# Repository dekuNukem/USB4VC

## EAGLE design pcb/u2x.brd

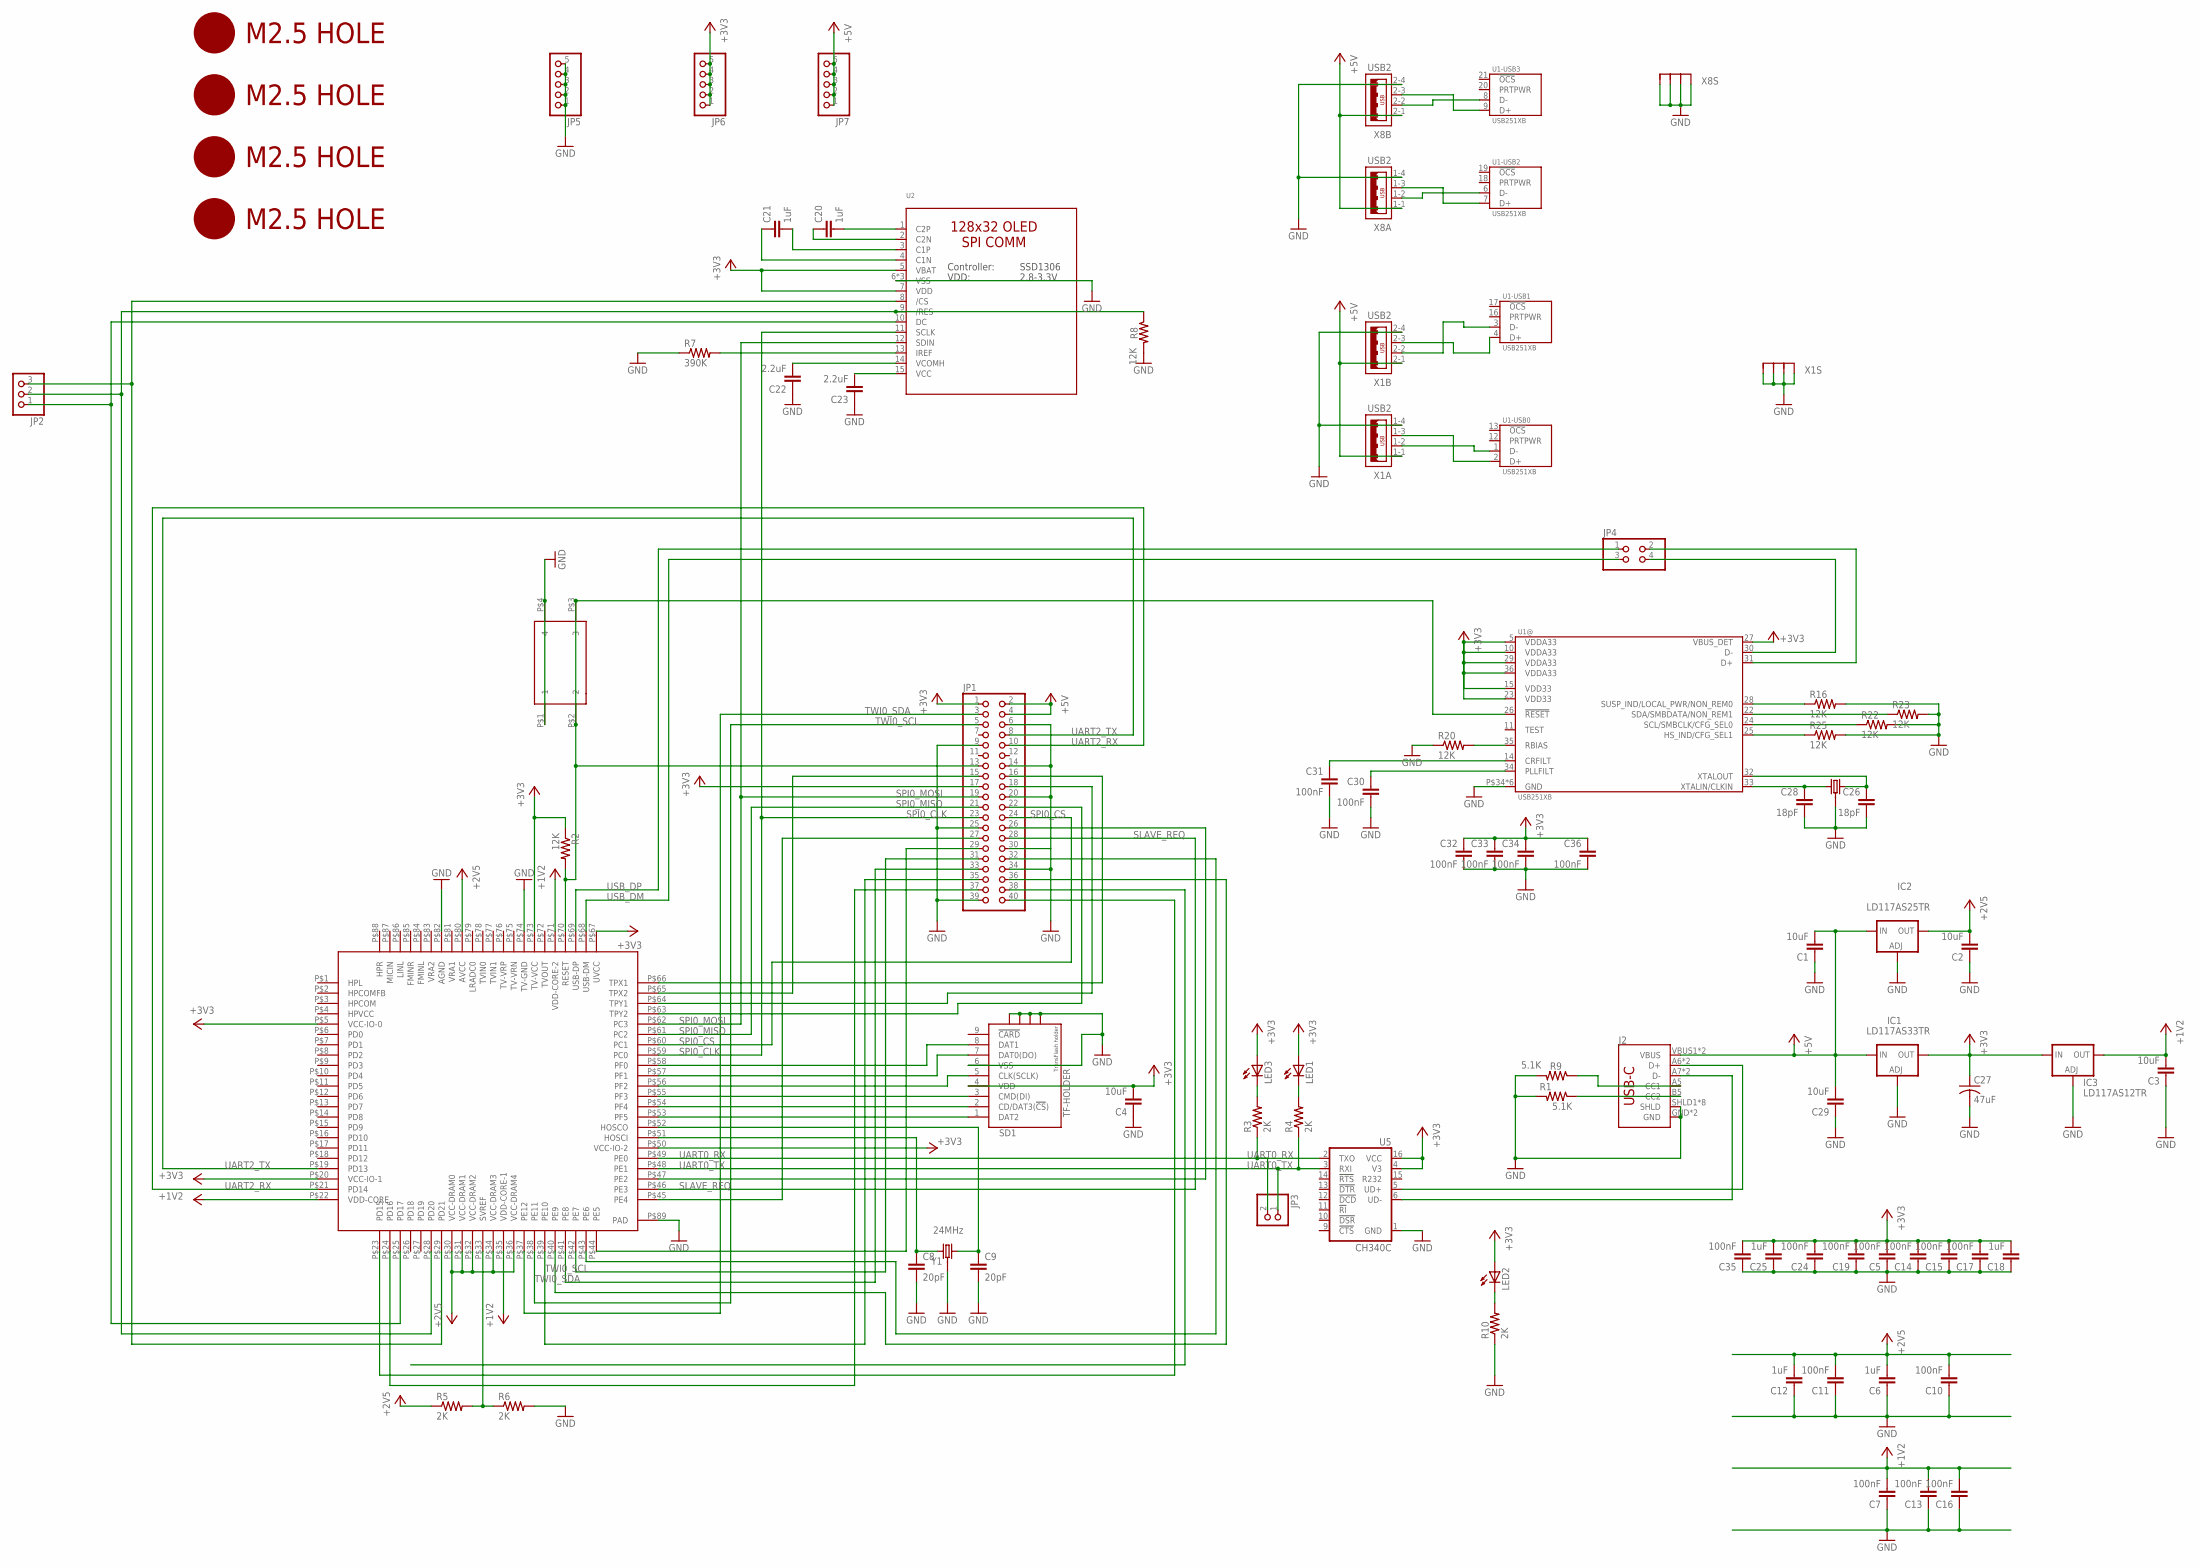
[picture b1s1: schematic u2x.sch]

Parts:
C1, C2, C3, C4, C29: 10uF; 0805
C5, C7, C10, C11, C13, C14, C15, C16, C17, C19, C24, C30, C31, C32, C33, C34, C35, C36: 100nF; 0805
C6, C12, C18, C20, C21, C25: 1uF; 0805
C8, C9: 20pF; 0805
C22, C23: 2.2uF; 0805
C26, C28: 18pF; 0805
C27: 47uF; C1210
IC1: LD117AS33TR; SOT223
IC2: LD117AS25TR; SOT223
IC3: LD117AS12TR; SOT223
J2: USB_C16PIN; USB-C-16P
JP1: PINHD-2X20-BIG; 2X20-BIG
JP2: PINHD-1X3CB; 1X03-CLEANBIG
JP3: PINHD-1X2; 1X02
JP4: PINHD-2X2; 2X02
JP5, JP6, JP7: PINHD-1X5; 1X05
LED1, LED2, LED3: LEDCHIP-LED0805; CHIP-LED0805
R1, R9: 5.1K; 0805
R2, R8, R16, R20, R22, R23, R25: 12K; 0805
R3, R4, R5, R6, R10: 2K; 0805
R7: 390K; 0805
SD1: TF-HOLDER; TF-PULL
SW20: 324_SW; 342_SWICH_FOOT
U1: USB251XB; QFN-36
U2: LUL_DISP_OLED_UG-2864HSWEG01; LUL_UG-2864HSWEG01_1.3_WRAPAROUND
U5: CH340C; SO016
U$1: F1C100S_DEV; MQFN88
U$2, U$3, U$4, U$5: M2.5HOLE
U$16: CRYSTAL-GROUNDED; CRYSTAL-SMD-5X3
X1, X8: USB2
Y1: 24MHz; CRYSTAL-SMD-3.2X2.5MM

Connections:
+1V2: C3.2, C7.2, C13.2, C16.2, IC3.4 (OUT), U$1.P$22 (VDD-CORE), U$1.P$35 (VDD-CORE-1), U$1.P$71 (VDD-CORE-2)
+2V5: C2.2, C6.2, C10.2, C11.2, C12.2, IC2.4 (OUT), R5.1, U$1.P$30 (VCC-DRAM0), U$1.P$31 (VCC-DRAM1), U$1.P$32 (VCC-DRAM2), U$1.P$34 (VCC-DRAM3), U$1.P$36 (VCC-DRAM4), U$1.P$80 (AVCC)
+3V3: C4.2, C5.2, C14.2, C15.2, C17.2, C18.2, C19.2, C24.2, C25.2, C27.1, C32.1, C33.1, C34.1, C35.2, C36.1, IC1.4 (OUT), IC3.3 (IN), JP1.1, JP1.17, JP6.1, JP6.2, JP6.3, JP6.4, JP6.5, LED1.A, LED2.A, LED3.A, R2.1, SD1.4 (VDD), U1.5 (VDDA33), U1.10 (VDDA33), U1.15 (VDD33), U1.23 (VDD33), U1.27 (VBUS_DET), U1.29 (VDDA33), U1.36 (VDDA33), U2.5 (VBAT), U2.7 (VDD), U5.4 (V3), U5.16 (VCC), U$1.P$5 (VCC-IO-0), U$1.P$20 (VCC-IO-1), U$1.P$50 (VCC-IO-2), U$1.P$67 (UVCC), U$1.P$73 (TV-VCC)
+5V: C1.2, C29.2, IC1.3 (IN), IC2.3 (IN), J2.VBUS1 (VBUS), J2.VBUS2 (VBUS), JP1.2, JP1.4, JP7.1, JP7.2, JP7.3, JP7.4, JP7.5, X1.1-1 (1), X1.2-1 (1), X8.1-1 (1), X8.2-1 (1)
GND: C1.1, C2.1, C3.1, C4.1, C5.1, C6.1, C7.1, C8.2, C9.2, C10.1, C11.1, C12.1, C13.1, C14.1, C15.1, C16.1, C17.1, C18.1, C19.1, C22.1, C23.1, C24.1, C25.1, C26.2, C27.2, C28.2, C29.1, C30.2, C31.2, C32.2, C33.2, C34.2, C35.1, C36.2, IC1.1 (ADJ), IC2.1 (ADJ), IC3.1 (ADJ), J2.GND, J2.GND2 (GND), J2.SHLD1 (SHLD), J2.SHLD2 (SHLD), J2.SHLD3 (SHLD), J2.SHLD4 (SHLD), J2.SHLD5 (SHLD), J2.SHLD6 (SHLD), J2.SHLD7 (SHLD), J2.SHLD8 (SHLD), JP1.6, JP1.9, JP1.14, JP1.20, JP1.25, JP1.30, JP1.34, JP1.39, JP5.1, JP5.2, JP5.3, JP5.4, JP5.5, R1.2, R6.2, R7.1, R8.2, R9.2, R10.1, R16.2, R20.1, R22.2, R23.2, R25.2, SD1.6 (VSS), SD1.S1, SD1.S2, SD1.S3, SD1.S4, SW20.P$1 (1), SW20.P$4 (4), U1.P$34 (GND), U1.P$35 (GND), U1.P$36 (GND), U1.P$37 (GND), U1.P$38 (GND), U1.PAD (GND), U2.6 (VSS), U2.16 (VSS), U2.17 (VSS), U5.1 (GND), U$1.P$74 (TV-GND), U$1.P$82 (AGND), U$1.P$89 (PAD), U$16.2 (3), U$16.4 (3), X1.1-4 (4), X1.2-4 (4), X1.M1 (S1), X1.M2 (S2), X1.M3 (S3), X1.M4 (S4), X8.1-4 (4), X8.2-4 (4), X8.M1 (S1), X8.M2 (S2), X8.M3 (S3), X8.M4 (S4), Y1.2 (3), Y1.4 (3)
unnamed: SD1.8 (DAT1), U$1.P$58 (PF0)
unnamed: J2.A5 (CC1), R9.1
unnamed: C8.1, U$1.P$51 (HOSCI), Y1.1
unnamed: C9.1, U$1.P$52 (HOSCO), Y1.3 (2)
unnamed: LED1.C, R4.2
unnamed: LED3.C, R3.2
unnamed: J2.B5 (CC2), R1.1
unnamed: SD1.7 (DAT0(DO)), U$1.P$57 (PF1)
unnamed: SD1.5 (CLK(SCLK)), U$1.P$56 (PF2)
unnamed: SD1.3 (CMD(DI)), U$1.P$55 (PF3)
unnamed: SD1.2 (CD/DAT3(!CS!)), U$1.P$54 (PF4)
unnamed: SD1.1 (DAT2), U$1.P$53 (PF5)
unnamed: U1.2 (D+), X1.1-3 (3)
unnamed: R5.2, R6.1, U$1.P$33 (SVREF)
unnamed: U1.1 (D-), X1.1-2 (2)
unnamed: J2.A6 (D+), J2.B6 (D+), U5.5 (UD+)
unnamed: JP1.13, R2.2, SW20.P$2 (2), SW20.P$3 (3), U1.26 (!RESET), U$1.P$70 (RESET)
unnamed: J2.A7 (D-), J2.B7 (D-), U5.6 (UD-)
unnamed: JP1.26, U$1.P$47 (PE2)
unnamed: JP1.27, U$1.P$45 (PE4)
unnamed: JP1.18, U$1.P$64 (TPY1)
unnamed: JP1.22, U$1.P$63 (TPY2)
unnamed: JP1.15, U$1.P$65 (TPX2)
unnamed: JP1.16, U$1.P$66 (TPX1)
unnamed: JP1.29, U$1.P$44 (PE5)
unnamed: JP1.32, U$1.P$43 (PE6)
unnamed: JP1.31, U$1.P$42 (PE7)
unnamed: JP1.33, U$1.P$41 (PE8)
unnamed: JP1.36, U$1.P$40 (PE9)
unnamed: JP1.35, U$1.P$39 (PE10)
unnamed: JP1.40, U$1.P$23 (PD15)
unnamed: JP1.37, U$1.P$24 (PD16)
unnamed: C20.2, U2.1 (C2P)
unnamed: C20.1, U2.2 (C2N)
unnamed: C21.2, U2.3 (C1P)
unnamed: C21.1, U2.4 (C1N)
unnamed: R7.2, U2.13 (IREF)
unnamed: C22.2, U2.14 (VCOMH)
unnamed: C23.2, U2.15 (VCC)
unnamed: JP2.3, U2.8 (/CS), U$1.P$29 (PD21)
unnamed: JP2.2, R8.1, U2.9 (/RES), U$1.P$28 (PD20)
unnamed: JP2.1, U2.10 (DC), U$1.P$25 (PD17)
unnamed: U1.4 (D+), X1.2-3 (3)
unnamed: U1.3 (D-), X1.2-2 (2)
unnamed: U1.6 (D-), X8.1-2 (2)
unnamed: U1.7 (D+), X8.1-3 (3)
unnamed: U1.8 (D-), X8.2-2 (2)
unnamed: U1.9 (D+), X8.2-3 (3)
unnamed: JP4.4, U1.30 (D-)
unnamed: JP4.2, U1.31 (D+)
unnamed: LED2.C, R10.2
unnamed: R20.2, U1.35 (RBIAS)
unnamed: C28.1, U1.33 (XTALIN/CLKIN), U$16.1 (2)
unnamed: C26.1, U1.32 (XTALOUT), U$16.3 (1)
unnamed: C31.1, U1.14 (CRFILT)
unnamed: C30.1, U1.34 (PLLFILT)
unnamed: R16.1, U1.28 (SUSP_IND/LOCAL_PWR/NON_REM0)
unnamed: R25.1, U1.25 (HS_IND/CFG_SEL1)
unnamed: R23.1, U1.22 (SDA/SMBDATA/NON_REM1)
unnamed: R22.1, U1.24 (SCL/SMBCLK/CFG_SEL0)
SLAVE_REQ: JP1.28, U$1.P$46 (PE3)
SPI0_CLK: JP1.23, U2.11 (SCLK), U$1.P$59 (PC0)
SPI0_CS: JP1.24, U$1.P$60 (PC1)
SPI0_MISO: JP1.21, U$1.P$61 (PC2)
SPI0_MOSI: JP1.19, U2.12 (SDIN), U$1.P$62 (PC3)
TWI0_SCL: JP1.5, U$1.P$38 (PE11)
TWI0_SDA: JP1.3, U$1.P$37 (PE12)
UART0_RX: JP3.2, R3.1, U5.2 (TXO), U$1.P$49 (PE0)
UART0_TX: JP3.1, R4.1, U5.3 (RXI), U$1.P$48 (PE1)
UART2_RX: JP1.10, U$1.P$21 (PD14)
UART2_TX: JP1.8, U$1.P$19 (PD13)
USB_DM: JP4.3, U$1.P$68 (USB-DM)
USB_DP: JP4.1, U$1.P$69 (USB-DP)

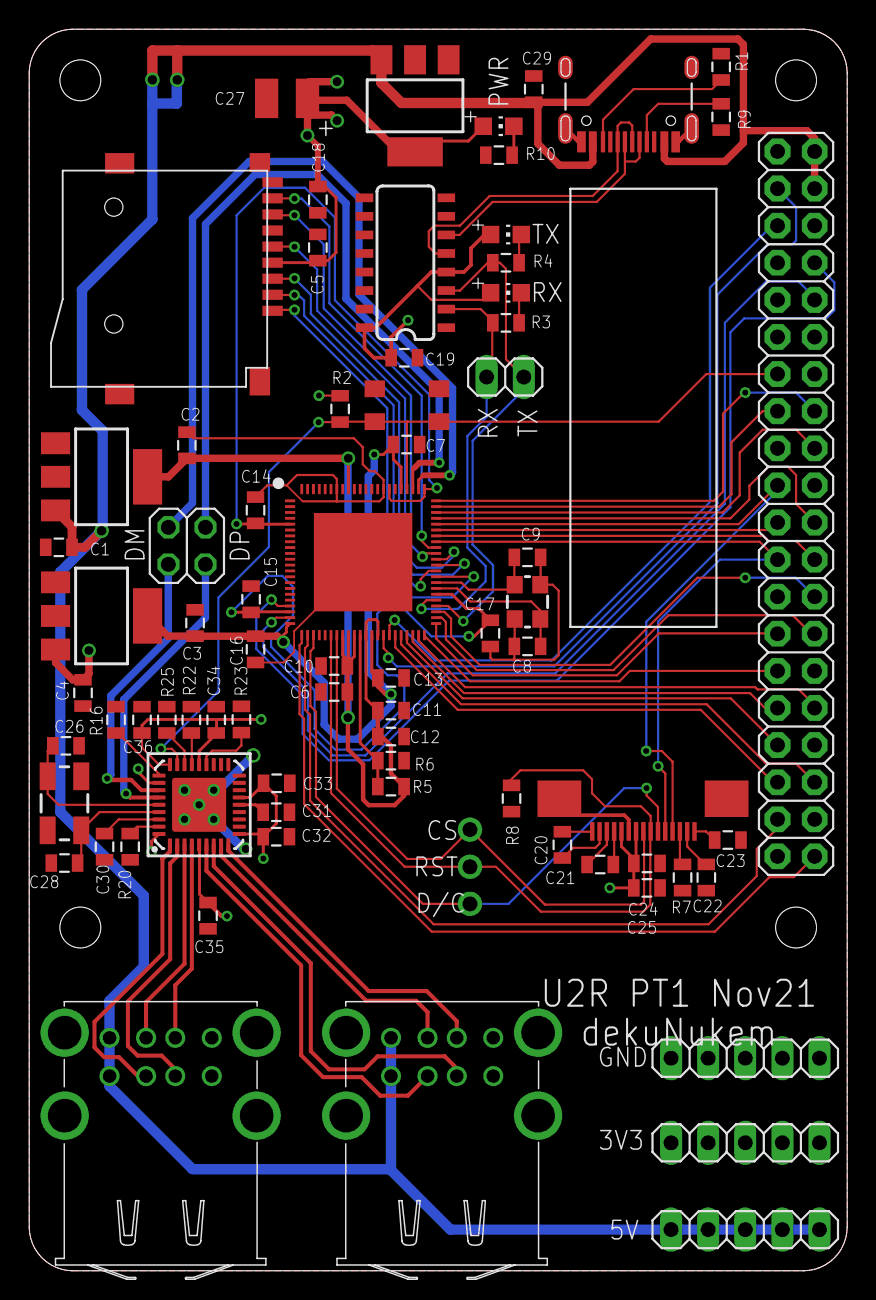
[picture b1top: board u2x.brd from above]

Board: 2 copper layers, 56.0 x 85.0 mm, 79 parts (0 on the bottom side), 78 nets.

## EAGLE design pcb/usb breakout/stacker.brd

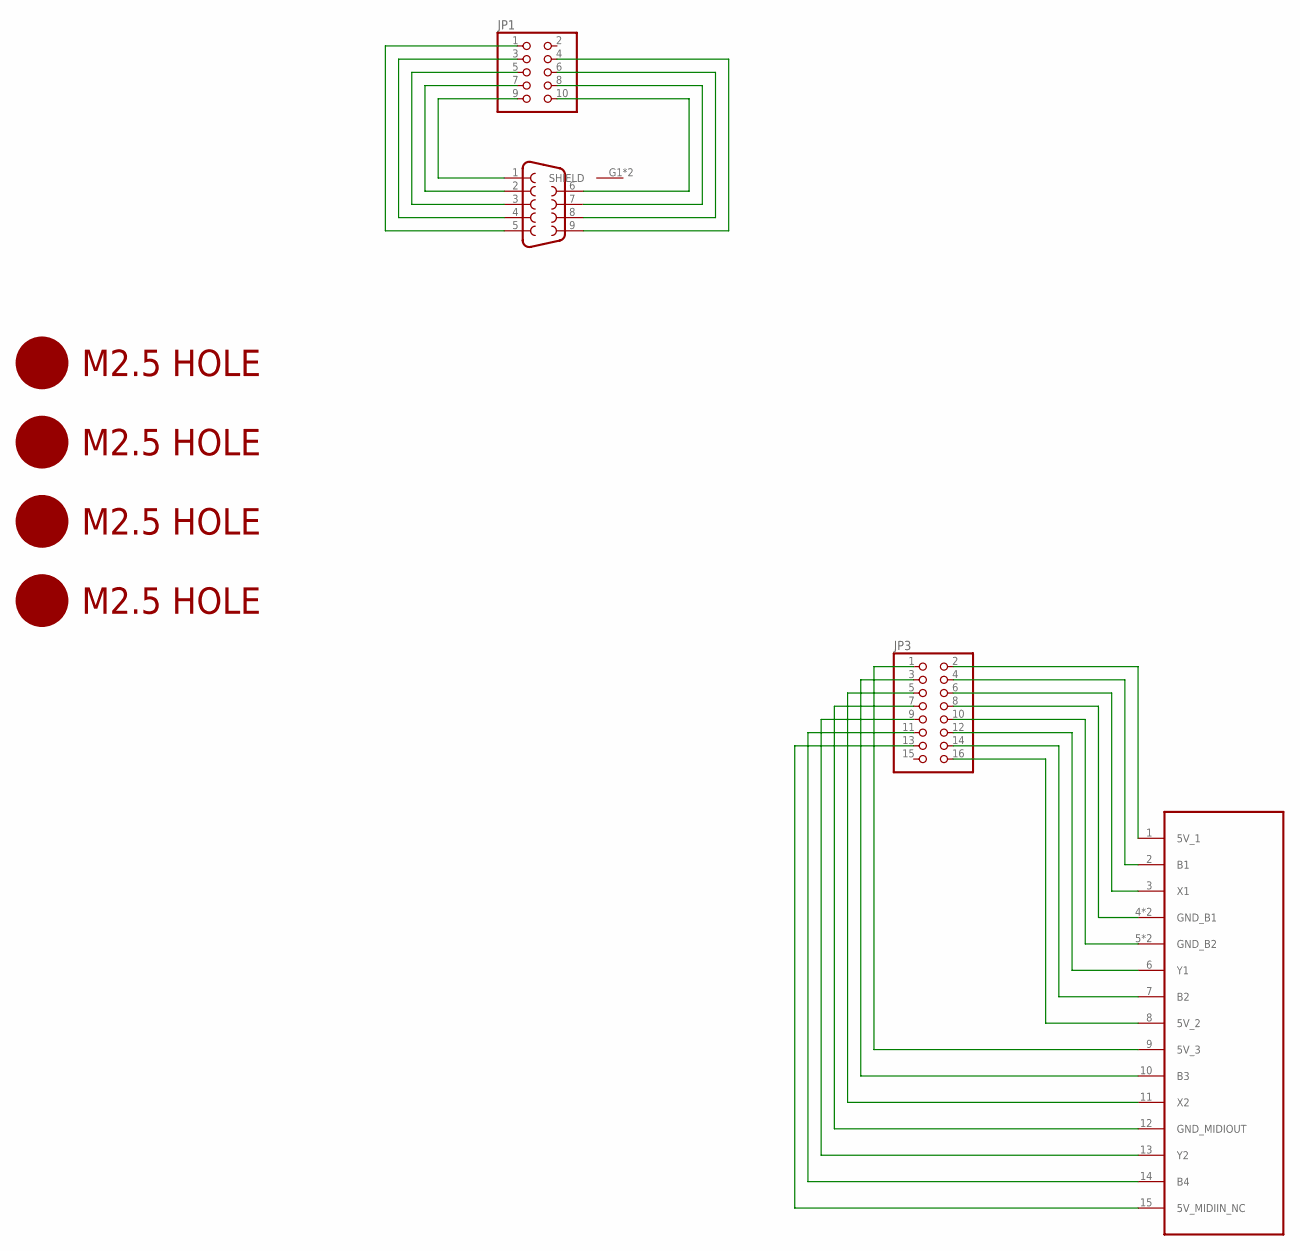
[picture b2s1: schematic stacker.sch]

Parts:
J5: DB9MALE; DB9_MALE
JP1: PINHD-2X5; 2X05
JP3: PINHD-2X8; 2X08
U$2, U$3, U$4, U$5: M2.5HOLE
U$11: GAMEPORT_15P; DA15

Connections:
unnamed: J5.1, JP1.9
unnamed: J5.2, JP1.7
unnamed: J5.3, JP1.5
unnamed: J5.4, JP1.3
unnamed: J5.5, JP1.1
unnamed: J5.6, JP1.10
unnamed: J5.7, JP1.8
unnamed: J5.8, JP1.6
unnamed: J5.9, JP1.4
unnamed: JP3.2, U$11.1 (5V_1)
unnamed: JP3.4, U$11.2 (B1)
unnamed: JP3.6, U$11.3 (X1)
unnamed: JP3.8, U$11.4 (GND_B1), U$11.G1 (GND_B1)
unnamed: JP3.10, U$11.5 (GND_B2), U$11.G2 (GND_B2)
unnamed: JP3.12, U$11.6 (Y1)
unnamed: JP3.14, U$11.7 (B2)
unnamed: JP3.16, U$11.8 (5V_2)
unnamed: JP3.1, U$11.9 (5V_3)
unnamed: JP3.3, U$11.10 (B3)
unnamed: JP3.5, U$11.11 (X2)
unnamed: JP3.7, U$11.12 (GND_MIDIOUT)
unnamed: JP3.9, U$11.13 (Y2)
unnamed: JP3.11, U$11.14 (B4)
unnamed: JP3.13, U$11.15 (5V_MIDIIN_NC)

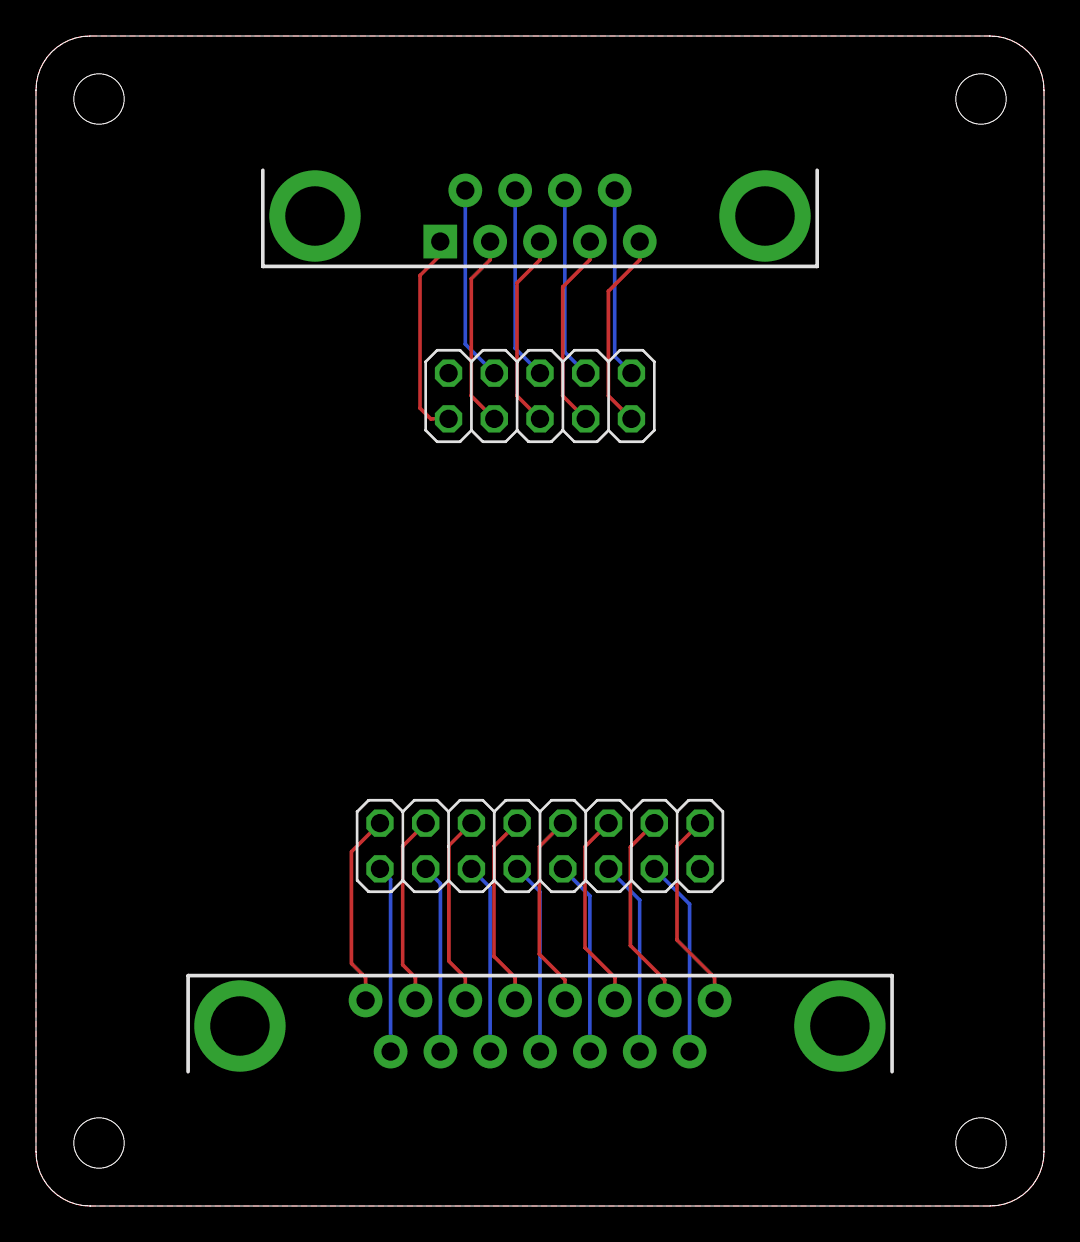
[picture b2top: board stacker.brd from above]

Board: 2 copper layers, 56.0 x 65.0 mm, 8 parts (0 on the bottom side), 24 nets.

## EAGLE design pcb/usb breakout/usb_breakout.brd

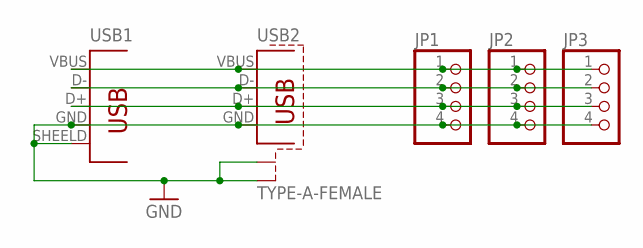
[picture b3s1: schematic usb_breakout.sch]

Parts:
JP1, JP2, JP3: PINHD-1X4; 1X04
USB1: TYPE-A-MALE-SHILED; TYPE-A-MALE
USB2: TYPE-A-FEMALE

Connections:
GND: JP1.4, JP2.4, JP3.4, USB1.GND (4), USB1.SHEELD (5), USB2.GND, USB2.S1, USB2.S2
unnamed: JP1.1, JP2.1, JP3.1, USB1.VBUS (1), USB2.VBUS (VCC)
unnamed: JP1.2, JP2.2, JP3.2, USB1.D- (2), USB2.D-
unnamed: JP1.3, JP2.3, JP3.3, USB1.D+ (3), USB2.D+

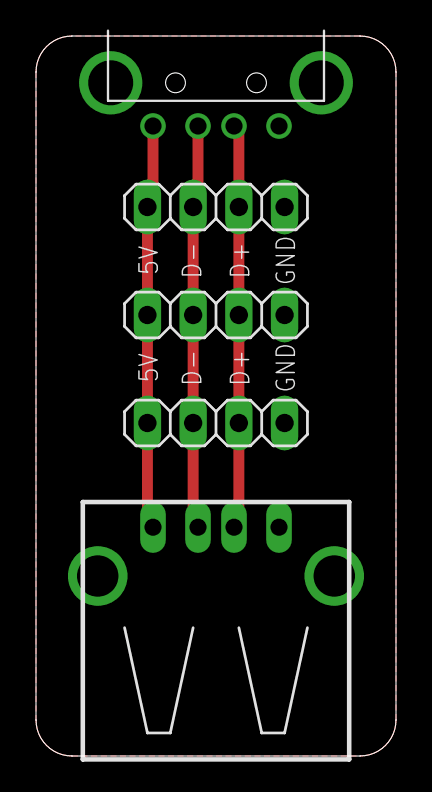
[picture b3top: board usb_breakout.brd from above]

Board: 2 copper layers, 20.0 x 40.0 mm, 5 parts (0 on the bottom side), 4 nets.

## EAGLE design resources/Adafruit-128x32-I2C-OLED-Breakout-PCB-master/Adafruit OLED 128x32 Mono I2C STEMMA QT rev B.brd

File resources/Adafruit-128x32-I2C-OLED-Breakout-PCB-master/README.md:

# PCB for the Adafruit 128x32 I2C OLED breakout board

<a href="http://www.adafruit.com/products/931"><br/>Click here to purchase one from the Adafruit shop</a>

__Format is EagleCAD schematic and board layout__

These displays are small, only about 1" diagonal, but very readable due to the high contrast of an OLED display. This display is made of 128x32 individual white OLED pixels, each one is turned on or off by the controller chip. Because the display makes its own light, no backlight is required. This reduces the power required to run the OLED and is why the display has such high contrast; we really like this miniature display for its crispness!

The driver chip SSD1306, __communicates via I2C only.__ 3 pins are required to communicate with the chip in the OLED display, two of which are I2C data/clock pins.

The OLED and driver require a 3.3V power supply and 3.3V logic levels for communication. To make it easier for our customers to use, we've added a 3.3v regulator and level shifter on board! This makes it compatible with any 5V microcontroller, such as the Arduino.

The power requirements depend a little on how much of the display is lit but on average the display uses about 20mA from the 3.3V supply. Built into the OLED driver is a simple switch-cap charge pump that turns 3.3v-5v into a high voltage drive for the OLEDs, making it one of the easiest ways to get an OLED into your project!

Of course, we wouldn't leave you with a datasheet and a "good luck": [We have a detailed tutorial](http://learn.adafruit.com/monochrome-oled-breakouts) and [example code in the form of an Arduino library](https://github.com/adafruit/Adafruit_SSD1306) for text and graphics. You'll need a microcontroller with more than 512 bytes of RAM since the display must be buffered.

You can download our SSD1306 OLED display Arduino library from github which comes with example code. The library can print text, bitmaps, pixels, rectangles, circles and lines. It uses 512 bytes of RAM since it needs to buffer the entire display but its very fast! The code is simple to adapt to any other microcontroller.

## License
Adafruit invests time and resources providing this open source design,
please support Adafruit and open-source hardware by purchasing
products from Adafruit!

Designed by Limor Fried/Ladyada for Adafruit Industries.
Creative Commons Attribution, Share-Alike license, check license.txt for more information
All text above must be included in any redistribution

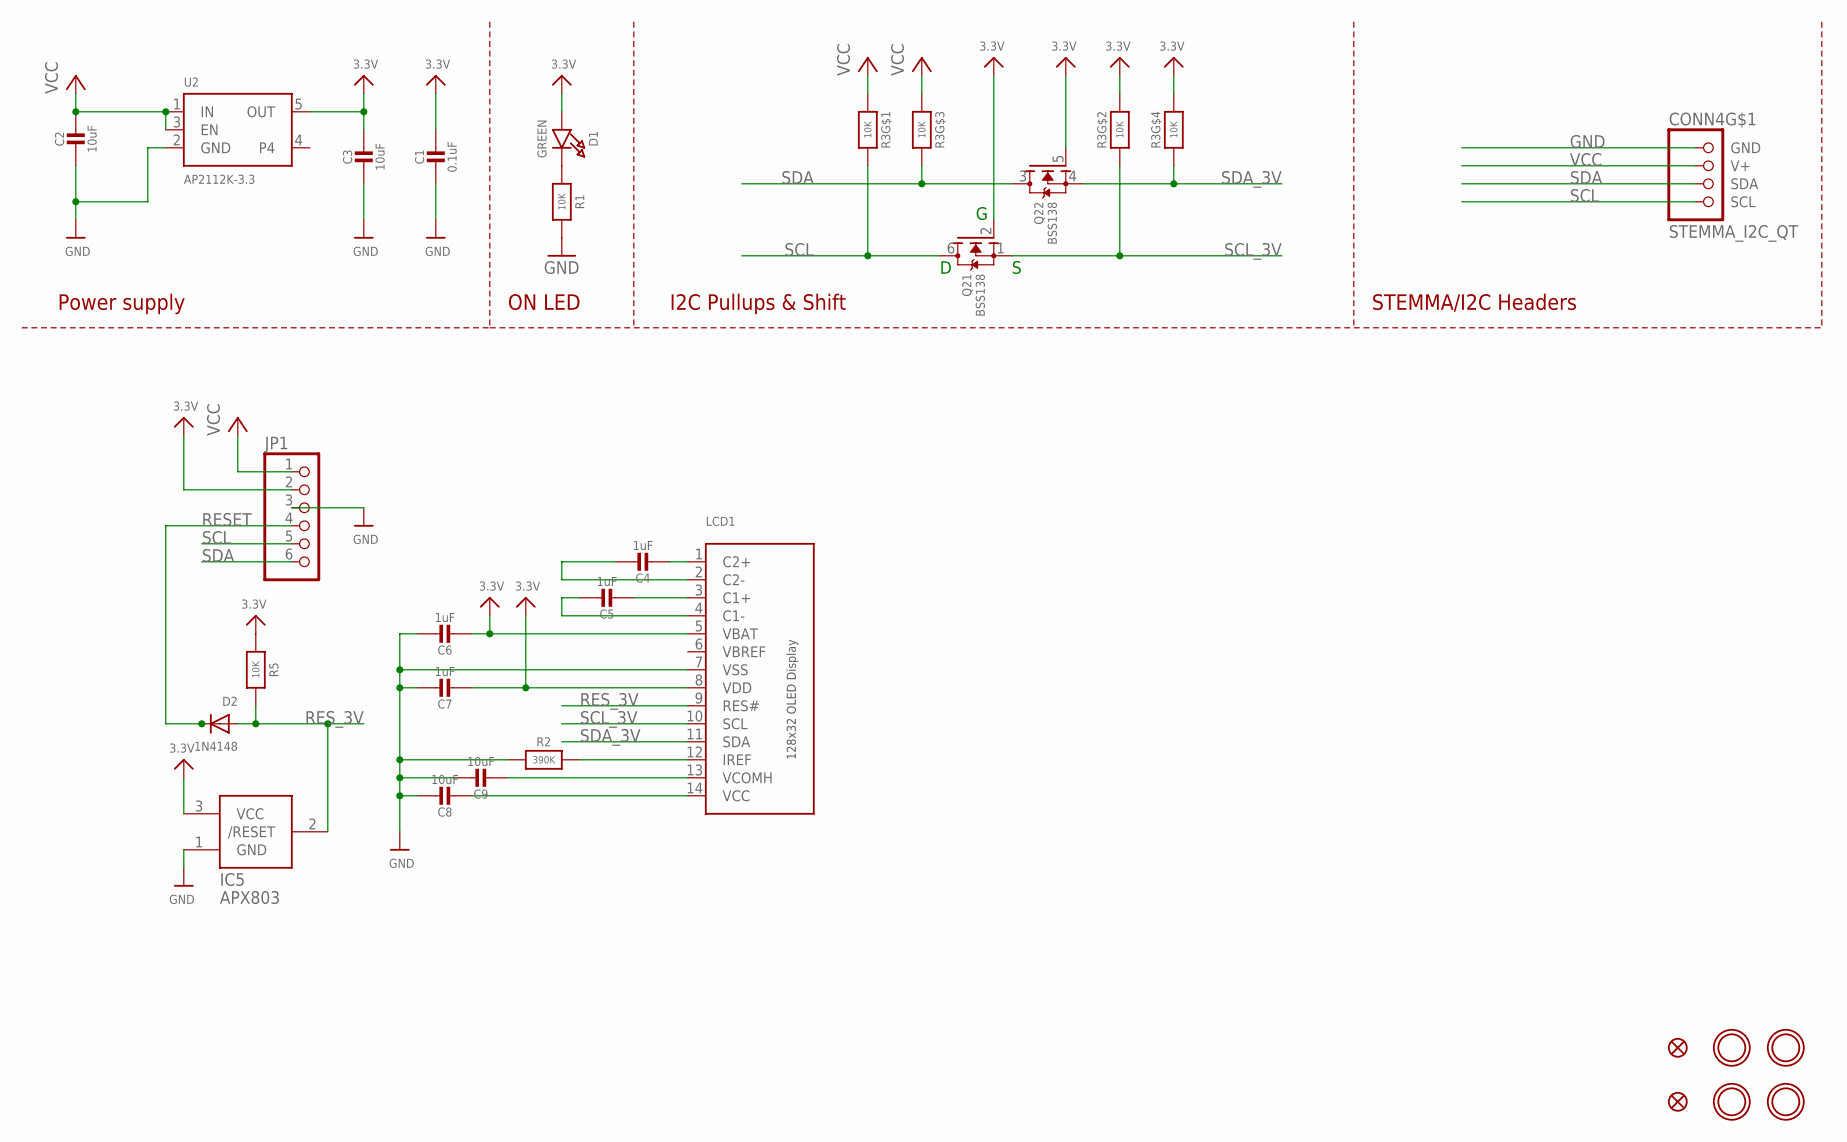
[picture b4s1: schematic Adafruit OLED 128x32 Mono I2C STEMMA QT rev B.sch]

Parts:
C1: 0.1uF; 0603-NO
C2, C3, C8, C9: 10uF; 0805-NO
C4, C5, C6, C7: 1uF; 0805-NO
CONN4: STEMMA_I2C_QT; JST_SH4
D1: GREEN; CHIPLED_0603_NOOUTLINE
D2: 1N4148; SOD-323F
FID3, FID4: FIDUCIAL_1MM
IC5: APX803; SOT23
JP1: HEADER-1X670MIL; 1X06_ROUND_70
LCD1: DISP_OLED_UG-2832HSWEG02; UG-2832HSWEG02_WRAPUNDER
Q2: BSS138; SOT363
R1, R5: 10K; 0603-NO
R2: 390K; 0603-NO
R3: 10K; RESPACK_4X0603
U2: AP2112K-3.3; SOT23-5
U$1, U$17, U$19, U$21: MOUNTINGHOLE2.5; MOUNTINGHOLE_2.5_PLATED

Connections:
3.3V: C1.1, C3.1, C6.2, C7.2, D1.A, IC5.3 (VCC), JP1.2, LCD1.5 (VBAT), LCD1.8 (VDD), Q2.2 (G), Q2.5 (G), R3.2 (1), R3.4 (1), R5.2, U2.5 (OUT)
GND: C1.2, C2.2, C3.2, C6.1, C7.1, C8.1, C9.1, CONN4.1 (GND), IC5.1 (GND), JP1.3, LCD1.7 (VSS), R1.2, R2.1, U2.2 (GND)
unnamed: C4.2, LCD1.1 (C2+)
unnamed: D1.C, R1.1
unnamed: C4.1, LCD1.2 (C2-)
unnamed: C5.2, LCD1.3 (C1+)
unnamed: C5.1, LCD1.4 (C1-)
unnamed: C9.2, LCD1.13 (VCOMH)
unnamed: LCD1.12 (IREF), R2.2
unnamed: C8.2, LCD1.14 (VCC)
RESET: D2.C, JP1.4
RES_3V: D2.A, IC5.2 (/RESET), LCD1.9 (RES#), R5.1
SCL: CONN4.4 (SCL), JP1.5, Q2.6 (D), R3.8 (2)
SCL_3V: LCD1.10 (SCL), Q2.1 (S), R3.7 (2)
SDA: CONN4.3 (SDA), JP1.6, Q2.3 (D), R3.6 (2)
SDA_3V: LCD1.11 (SDA), Q2.4 (S), R3.5 (2)
VBREF: LCD1.6 (VBREF)
VCC: C2.1, CONN4.2 (V+), JP1.1, R3.1, R3.3 (1), U2.1 (IN), U2.3 (EN)

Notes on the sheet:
I2C Pullups & Shift
STEMMA/I2C Headers
ON LED
Power supply

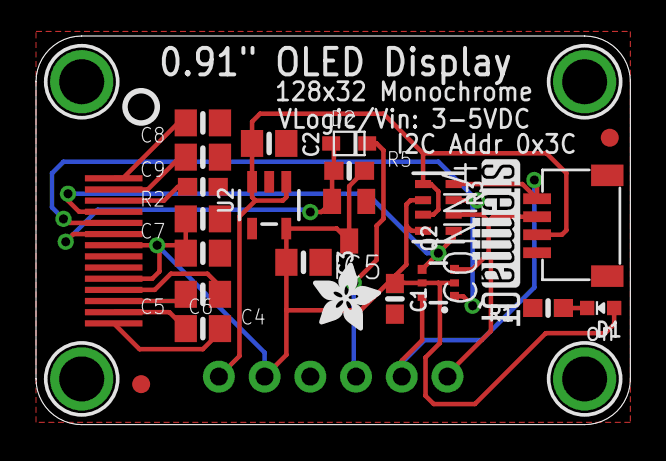
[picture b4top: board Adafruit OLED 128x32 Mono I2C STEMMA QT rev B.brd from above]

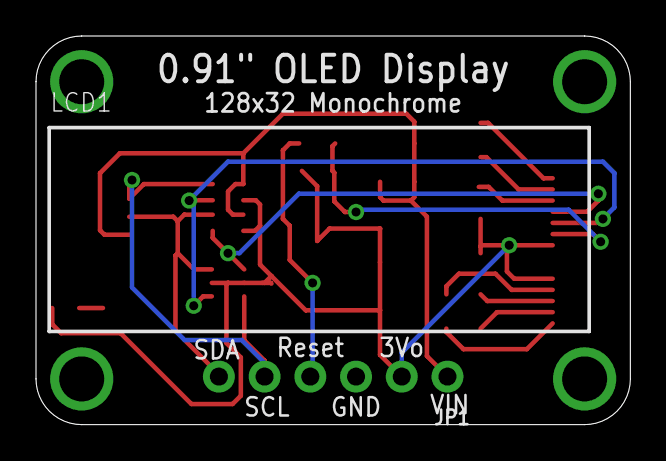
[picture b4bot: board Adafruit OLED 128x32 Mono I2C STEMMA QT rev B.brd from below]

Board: 2 copper layers, 33.0 x 21.6 mm, 30 parts (2 on the bottom side), 17 nets.

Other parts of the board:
U$22: ADAFRUIT_3.5MM
U$25: PCBFEAT-REV-040
U$31: STEMMAQT

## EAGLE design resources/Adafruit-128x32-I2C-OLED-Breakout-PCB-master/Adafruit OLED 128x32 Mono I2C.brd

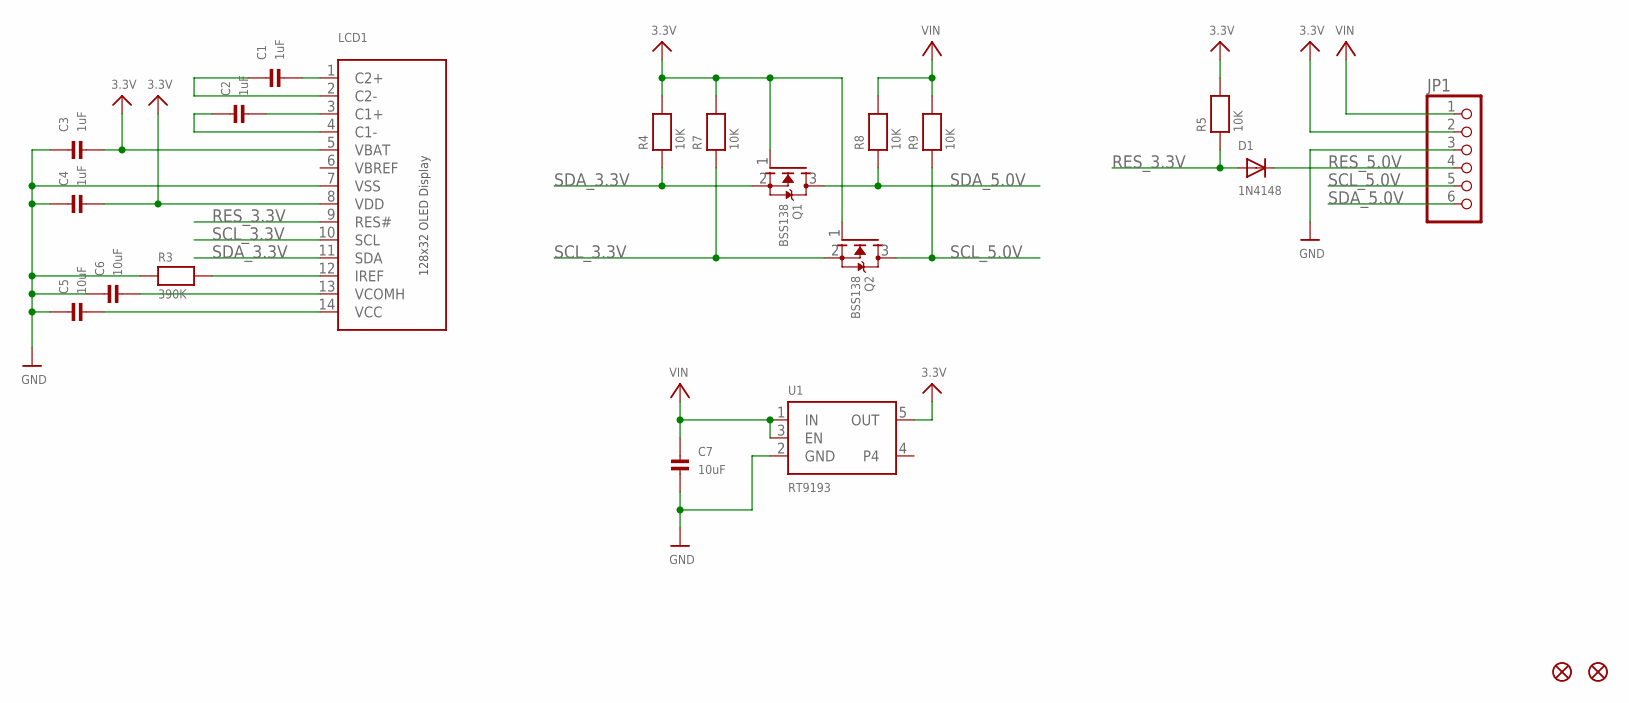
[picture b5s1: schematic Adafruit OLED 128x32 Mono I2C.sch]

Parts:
C1, C2, C3, C4: 1uF; 0805
C5, C6, C7: 10uF; 0805
D1: 1N4148; SOD-323F
FID1, FID2: FIDUCIAL""; FIDUCIAL_1MM
JP1: HEADER-1X670MIL; 1X06_ROUND_70
LCD1: DISP_OLED_UG-2832HSWEG02; UG-2832HSWEG02_WRAPUNDER
Q1, Q2: BSS138; SOT23-WIDE
R3: 390K; 0805
R4, R5, R7, R8, R9: 10K; 0805
U1: RT9193; SOT23-5

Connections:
3.3V: C3.2, C4.2, JP1.2, LCD1.5 (VBAT), LCD1.8 (VDD), Q1.1 (G), Q2.1 (G), R4.2, R5.2, R7.2, U1.5 (OUT)
GND: C3.1, C4.1, C5.1, C6.1, C7.2, JP1.3, LCD1.7 (VSS), R3.1, U1.2 (GND)
unnamed: C1.2, LCD1.1 (C2+)
unnamed: C1.1, LCD1.2 (C2-)
unnamed: C2.2, LCD1.3 (C1+)
unnamed: C2.1, LCD1.4 (C1-)
unnamed: C6.2, LCD1.13 (VCOMH)
unnamed: C5.2, LCD1.14 (VCC)
unnamed: LCD1.12 (IREF), R3.2
RES_3.3V: D1.A, LCD1.9 (RES#), R5.1
RES_5.0V: D1.C, JP1.4
SCL_3.3V: LCD1.10 (SCL), Q2.2 (S), R7.1
SCL_5.0V: JP1.5, Q2.3 (D), R9.1
SDA_3.3V: LCD1.11 (SDA), Q1.2 (S), R4.1
SDA_5.0V: JP1.6, Q1.3 (D), R8.1
VBREF: LCD1.6 (VBREF)
VIN: C7.1, JP1.1, R8.2, R9.2, U1.1 (IN), U1.3 (EN)

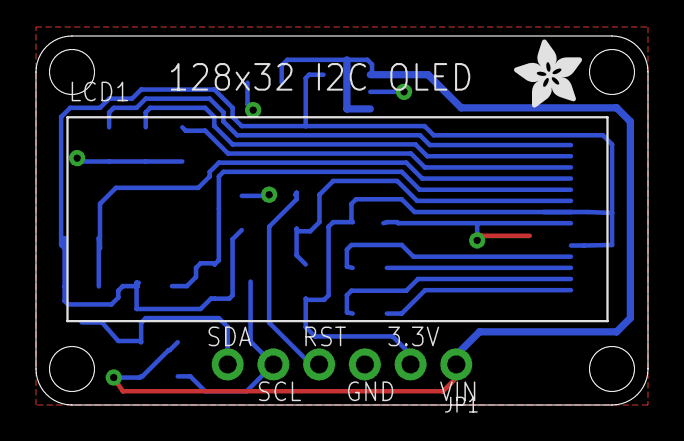
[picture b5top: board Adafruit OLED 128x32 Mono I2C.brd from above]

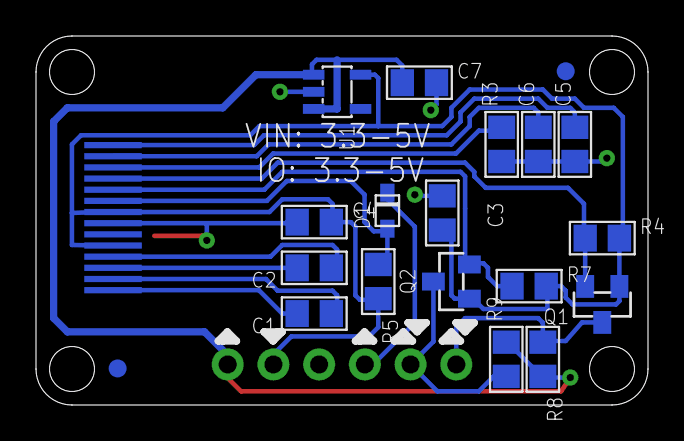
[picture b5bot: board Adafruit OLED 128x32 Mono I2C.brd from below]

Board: 2 copper layers, 34.0 x 20.5 mm, 22 parts (19 on the bottom side), 16 nets.

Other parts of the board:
U$16: ADAFRUIT_3.5MM

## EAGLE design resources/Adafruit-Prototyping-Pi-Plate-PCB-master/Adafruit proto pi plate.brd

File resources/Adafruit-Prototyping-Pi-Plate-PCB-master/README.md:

# Adafruit Prototyping Pi Plate

<a href="http://www.adafruit.com/products/801"><br/>Click here to purchase one from the Adafruit shop</a>

These are the Eagle CAD files for the Adafruit Prototyping Pi Plate.

Now that you've finally got your hands on a [Raspberry Pi®](http://www.raspberrypi.org/) , you're probably itching to make some fun embedded computer projects with it. What you need is an add on prototyping Pi Plate from Adafruit, which can snap onto the Pi PCB (and is removable later if you wish) and gives you all sorts of prototyping goodness to make building on top of the Pi super easy.

__Note: This kit is best used for the Raspberry Pi Model A or Model B.__ You can use it with any "2x20 GPIO type" Pi  (A+, B+, Zero, Pi 2, Pi 3) but only the 'top 26 pins' will be broken out for use

We added lots of basic but essential goodies. First up, there's a big prototyping area, half of which is 'breadboard' style and half of which is 'perfboard' style so you can wire up DIP chips, sensors, and the like. Along the edges of the proto area, all the GPIO/I2C/SPI and power pins are broken out to 0.1" stips so you can easily connect to them. On the edges of the prototyping area, (almost all of) the breakout pins are also connected to labeled 3.5mm screw-terminal blocks. This makes it easy to semi-permanently wire in sensors, LEDs, etc. There's also a 4-block terminal block broken out to 0.1" pads for general non-GPIO wiring. Finally, we had a little space remaining over the metal connectors so we put in an SOIC surface mount chip breakout area, for those chips that dont come in DIP format.

__This kit comes as a set of parts, a little soldering is required to put it together but its really easy, even a beginner can do it in 15-20 minutes or so.__ The Pi (and our kits) are meant to help us all learn skills, soldering is fun! [Check out our tutorial for how to assemble](http://learn.adafruit.com/adafruit-prototyping-pi-plate).

The nice thing about this plate is we're getting custom header breakouts that are taller than usual, so that the proto plate sits above the metal connectors, out of the way and allows for plenty of workspace. It fits in our Pi Box enclosure with access to the terminal blocks so you can keep the Pi safe while prototyping. We'll have stackable header kits as well for those who want to put multiple plates on top.

For more information, including some usage ideas [check out our Proto Pi Plate tutorial](http://learn.adafruit.com/adafruit-prototyping-pi-plate).

Note: The terminal blocks included with your product may be blue or black.

### License

Adafruit invests time and resources providing this open source design, please support Adafruit and open-source hardware by purchasing products from Adafruit!

Designed by Limor Fried/Ladyada for Adafruit Industries.
CERN OPEN HARDWARE LICENSE v1.1 
http://www.ohwr.org/

All text above must be included in any redistribution

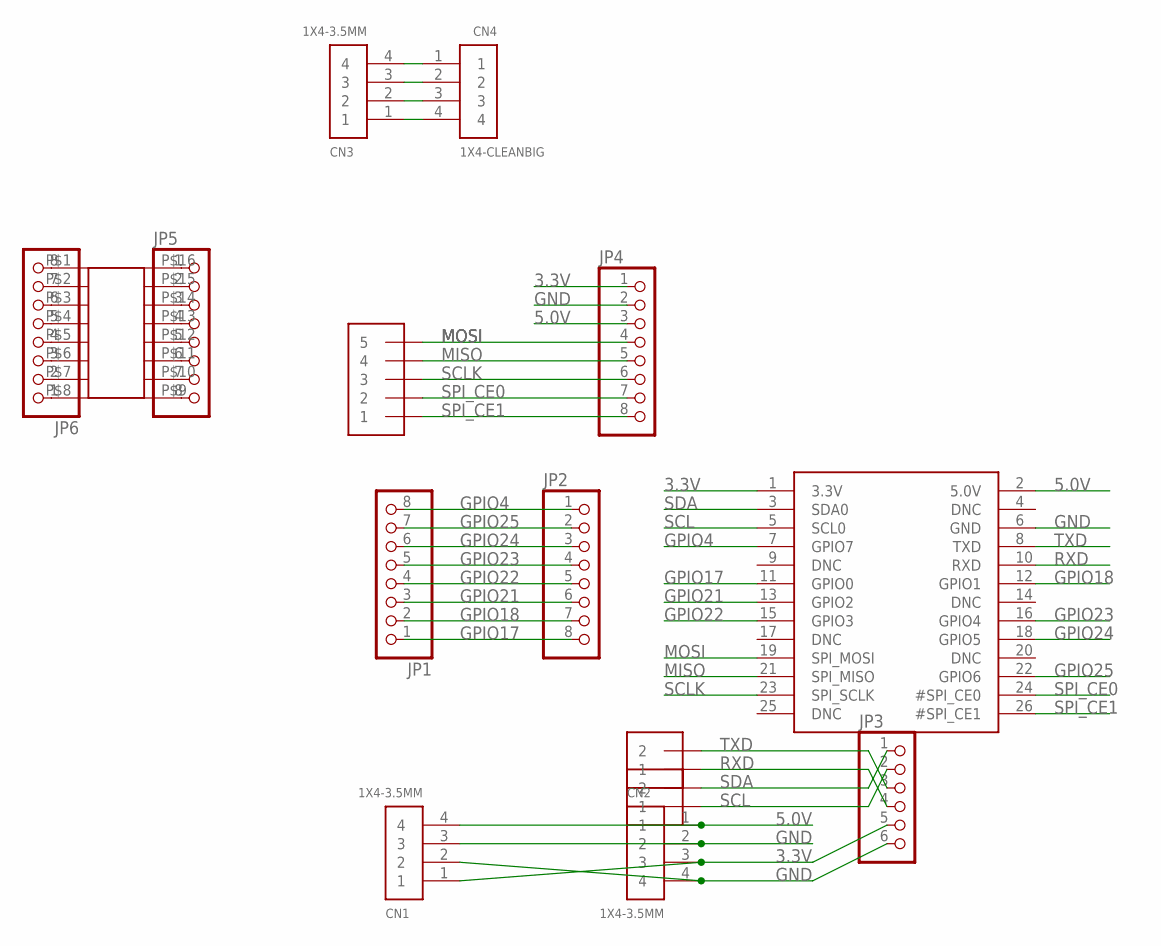
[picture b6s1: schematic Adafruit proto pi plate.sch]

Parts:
CN1, CN2, CN3: 1X4-3.5MM; 1X04-3.5MM
CN4: 1X4-CLEANBIG; 1X04-CLEANBIG
J1, J2: 1X2-3.5MM
J3: 1X5; 1X05-3.5MM
JP1: PINHD-1X8-3.5MM; 1X08-3.5MM
JP2, JP4, JP5, JP6: PINHD-1X8BIG; 1X08-BIG
JP3: PINHD-1X6B; 1X06-BIG
U$1: RASPBERRYPI_BB; RASBERRYPI_SHIELD
U$2: SMD-16SOIC; SO-16NMW

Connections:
3.3V: CN1.1, CN2.3, JP3.5, JP4.1, U$1.1 (3.3V)
5.0V: CN1.4, CN2.1, JP4.3, U$1.2 (5.0V)
GND: CN1.2, CN1.3, CN2.2, CN2.4, JP3.6, JP4.2, U$1.6 (GND)
GPIO4: JP1.8, JP2.1, U$1.7 (GPIO7)
GPIO17: JP1.1, JP2.8, U$1.11 (GPIO0)
GPIO18: JP1.2, JP2.7, U$1.12 (GPIO1)
GPIO21: JP1.3, JP2.6, U$1.13 (GPIO2)
GPIO22: JP1.4, JP2.5, U$1.15 (GPIO3)
GPIO23: JP1.5, JP2.4, U$1.16 (GPIO4)
GPIO24: JP1.6, JP2.3, U$1.18 (GPIO5)
GPIO25: JP1.7, JP2.2, U$1.22 (GPIO6)
MISO: J3.4, JP4.5, U$1.21 (SPI_MISO)
MOSI: J3.5, JP4.4, U$1.19 (SPI_MOSI)
unnamed: JP5.1, U$2.P$16
unnamed: JP5.2, U$2.P$15
unnamed: JP5.3, U$2.P$14
unnamed: JP5.4, U$2.P$13
unnamed: JP5.5, U$2.P$12
unnamed: JP5.6, U$2.P$11
unnamed: JP5.7, U$2.P$10
unnamed: JP5.8, U$2.P$9
unnamed: JP6.1, U$2.P$8
unnamed: JP6.2, U$2.P$7
unnamed: JP6.3, U$2.P$6
unnamed: JP6.4, U$2.P$5
unnamed: JP6.5, U$2.P$4
unnamed: JP6.6, U$2.P$3
unnamed: JP6.7, U$2.P$2
unnamed: JP6.8, U$2.P$1
unnamed: CN3.4, CN4.1
unnamed: CN3.3, CN4.2
unnamed: CN3.2, CN4.3
unnamed: CN3.1, CN4.4
RXD: J2.1, JP3.4, U$1.10 (RXD)
SCL: J1.1, JP3.2, U$1.5 (SCL0)
SCLK: J3.3, JP4.6, U$1.23 (SPI_SCLK)
SDA: J1.2, JP3.1, U$1.3 (SDA0)
SPI_CE0: J3.2, JP4.7, U$1.24 (#SPI_CE0)
SPI_CE1: J3.1, JP4.8, U$1.26 (#SPI_CE1)
TXD: J2.2, JP3.3, U$1.8 (TXD)

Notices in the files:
resources/Adafruit-Prototyping-Pi-Plate-PCB-master/Adafruit proto pi plate.brd:
Copyright (c) 2012
Licenced under
CERN OHL v1.1
parts and their libraries:
SparkFun-Connectors: Licensing: Creative Commons ShareAlike 4.0 International - https://creativecommons.org/licenses/by-sa/4.0
microbuilder: This work is placed in the public domain, and may be freely used for commercial and non-commercial work with the following conditions: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
